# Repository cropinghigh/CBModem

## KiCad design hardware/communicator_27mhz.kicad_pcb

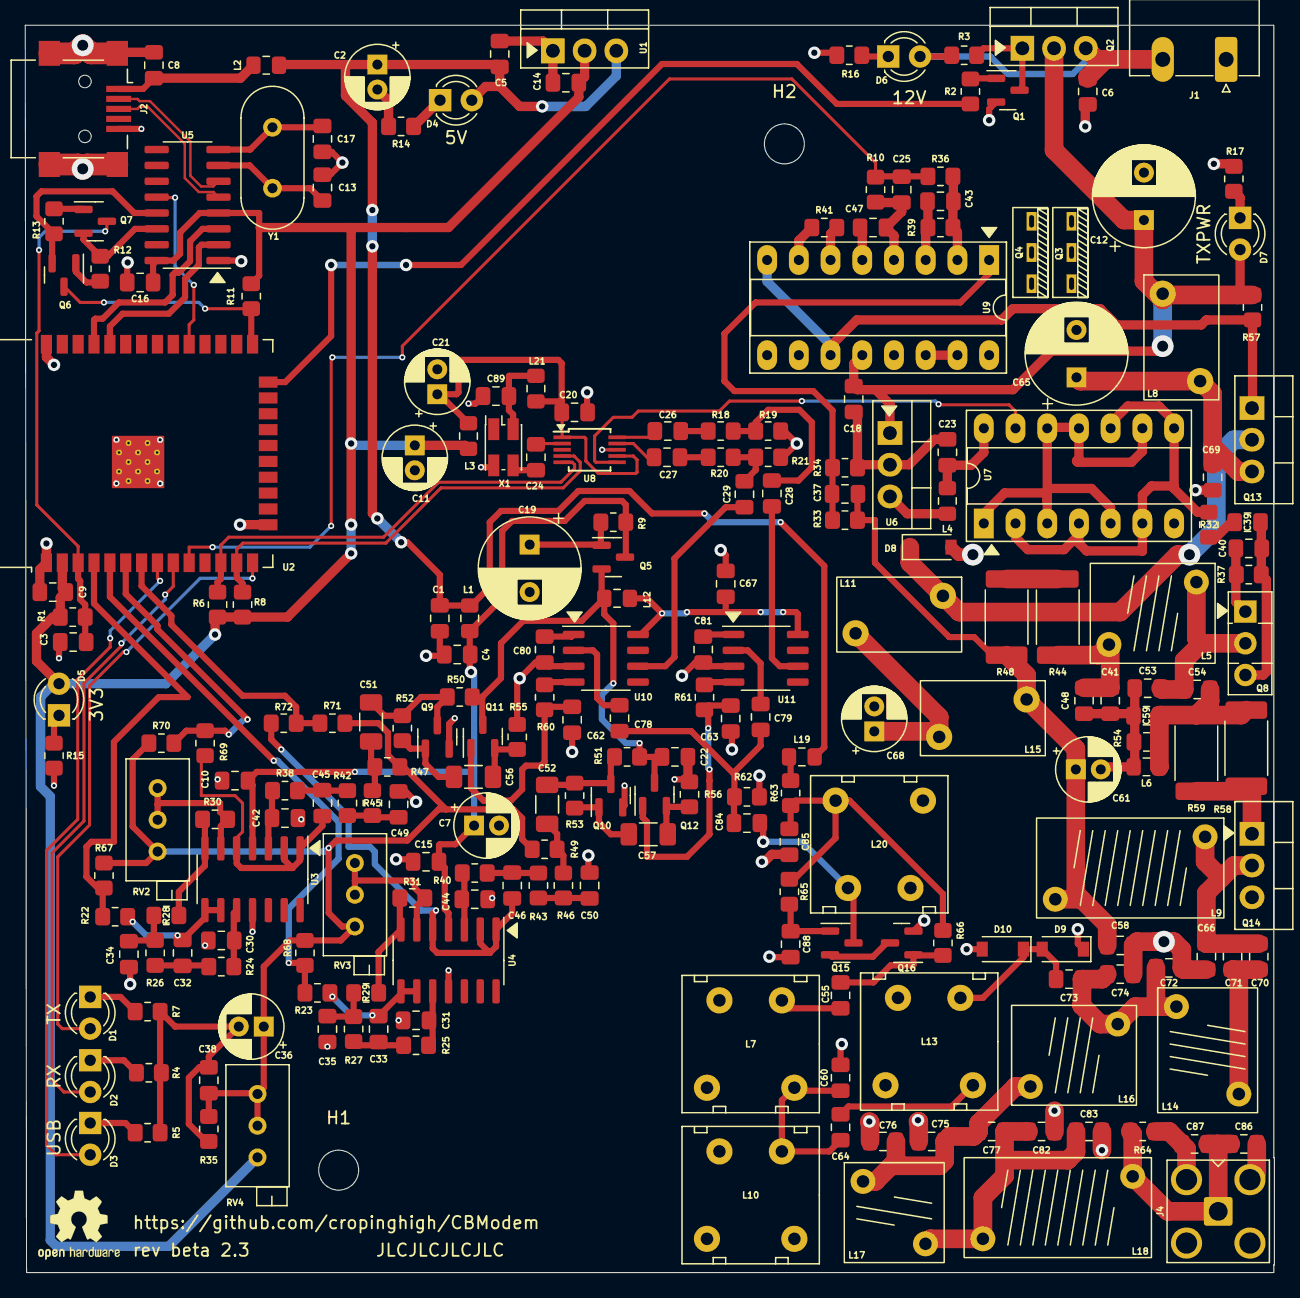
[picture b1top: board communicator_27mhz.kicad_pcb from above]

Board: 2 copper layers, 100.0 x 99.9 mm, 230 parts (0 on the bottom side), 132 nets.

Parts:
C1, C4, C5, C6, C8, C9, C10, C14, C15, C16, C18, C20, C23, C24, C26, C27, C28, C29, C38, C39, C43, C54, C58, C67, C69, C85, C89: 0.1u; C_0805_2012Metric_Pad1.18x1.45mm_HandSolder
C3: 2.2u; C_0805_2012Metric_Pad1.18x1.45mm_HandSolder
C7, C21, C36: 47u; CP_Radial_D5.0mm_P2.00mm
C11: 10u; CP_Radial_D5.0mm_P2.00mm
C12, C19: 470u; CP_Radial_D8.0mm_P3.80mm
C13, C17: 22p; C_0805_2012Metric_Pad1.18x1.45mm_HandSolder
C25, C32, C33, C34, C35, C45, C46, C49, C50, C62, C63, C78, C79, C80, C81, C88: 10n; C_0805_2012Metric_Pad1.18x1.45mm_HandSolder
C30, C31, C42, C44, C47: 1n; C_0805_2012Metric_Pad1.18x1.45mm_HandSolder
C37: 6n8; C_0805_2012Metric_Pad1.18x1.45mm_HandSolder
C40, C86: 150p; C_0805_2012Metric_Pad1.18x1.45mm_HandSolder
C41, C48: 47n; C_0805_2012Metric_Pad1.18x1.45mm_HandSolder
C51, C52, C56, C57: 10u; C_1206_3216Metric_Pad1.33x1.80mm_HandSolder
C53, C60, C72, C74, C75: 330p; C_0805_2012Metric_Pad1.18x1.45mm_HandSolder
C55, C64: 470p; C_0805_2012Metric_Pad1.18x1.45mm_HandSolder
C59, C66: 100p; C_0805_2012Metric_Pad1.18x1.45mm_HandSolder
C70, C71, C76, C82, C83: 220p; C_0805_2012Metric_Pad1.18x1.45mm_HandSolder
C73, C84: 47p; C_0805_2012Metric_Pad1.18x1.45mm_HandSolder
C77: 39p; C_0805_2012Metric_Pad1.18x1.45mm_HandSolder
C87: 30p; C_0805_2012Metric_Pad1.18x1.45mm_HandSolder
C?: 22u; CP_Radial_D8.0mm_P3.80mm
C?#2: 47u; CP_Radial_D5.0mm_P2.00mm
C?#3: 0.1u; C_0805_2012Metric_Pad1.18x1.45mm_HandSolder
C?#4, C?#5: 22u; CP_Radial_D5.0mm_P2.00mm
D1: TX; LED_D3.0mm
D2: RX; LED_D3.0mm
D3: USB; LED_D3.0mm
D4: 5V; LED_D3.0mm
D5: 3V3; LED_D3.0mm
D6: 12V; LED_D3.0mm
D7: TXPWR; LED_D3.0mm
D8, D9, D10: 4148; D_SOD-123
H1, H2: M3; MountingHole_3.2mm_M3
J1: EXT_12V; PhoenixContact_MC_1,5_2-G-5.08_1x02_P5.08mm_Horizontal
J2: USB_B_Micro; USB_Mini-B_Lumberg_2486_01_Horizontal
J4: ANT; SMA_Amphenol_901-143_Horizontal
L1, L2, L3, L4, L12, L19, L21: 10uH; L_0805_2012Metric_Pad1.15x1.40mm_HandSolder
L5: 0.15uH(6T,d6); Inductor_10x8
L6: 6.8uH; L_0805_2012Metric_Pad1.15x1.40mm_HandSolder
L7, L10: 220n; Soviet_inductor_core_vertical
L8, L15: ~40T on М2000НМ core; Ferrite_ring_10x6x5_vertical
L9: 0.5uH(13T,d5); Inductor_15x8
L11: 6T on М2000НМ core; Ferrite_ring_10x6x5_vertical
L13: 820n; Soviet_inductor_core_vertical
L14: 0.225uH(6T,d6); Inductor_10x8
L16: 6T, d=5; Inductor_10x8
L17: 7T, d=4; Inductor_8x8
L18: 10T, d=4mm; Inductor_15x8
L20: 3.7-20uH; Soviet_inductor_core_vertical
LOGO1: Logo_Open_Hardware_Large; OSHW-Logo2_7.3x6mm_SilkScreen
Q1: MMBT2222A; SOT-23
Q2, Q13: IRF9Z34N; TO-220-3_Vertical
Q3, Q4: KT315; KT-13
Q8: C2314; TO-126-3_Vertical
Q14: C2078; TO-220-3_Vertical
Q?: MMBT2222A; SOT-23
Q?#2, Q?#3, Q?#4, Q?#5, Q?#6, Q?#7, Q?#8, Q?#9: MMBT2222A; SOT-23
R1, R3, R11, R12, R13, R22, R23, R26, R27, R42, R43, R67, R68, R69, R70, R71, R72: 10k; R_0805_2012Metric_Pad1.20x1.40mm_HandSolder
R2: 50k; R_0805_2012Metric_Pad1.20x1.40mm_HandSolder
R4, R5, R6, R7, R8, R15: 1k; R_0805_2012Metric_Pad1.20x1.40mm_HandSolder
R9, R62: 680; R_0805_2012Metric_Pad1.20x1.40mm_HandSolder
R14: 2k; R_0805_2012Metric_Pad1.20x1.40mm_HandSolder
R16, R17, R34, R41, R47, R49, R50, R51: 5k; R_0805_2012Metric_Pad1.20x1.40mm_HandSolder
R18, R20: 6k8; R_0805_2012Metric_Pad1.20x1.40mm_HandSolder
R19, R21: 510; R_0805_2012Metric_Pad1.20x1.40mm_HandSolder
R24, R25, R38, R40: 5k6; R_0805_2012Metric_Pad1.20x1.40mm_HandSolder
R28, R29, R45, R46, R60, R61: 3k3; R_0805_2012Metric_Pad1.20x1.40mm_HandSolder
R30, R31: 20k; R_0805_2012Metric_Pad1.20x1.40mm_HandSolder
R32: 10; R_0805_2012Metric_Pad1.20x1.40mm_HandSolder
R35: 500; R_0805_2012Metric_Pad1.20x1.40mm_HandSolder
R36: 470; R_0805_2012Metric_Pad1.20x1.40mm_HandSolder
R37, R63: 100; R_0805_2012Metric_Pad1.20x1.40mm_HandSolder
R39, R52, R53: 100k; R_0805_2012Metric_Pad1.20x1.40mm_HandSolder
R44, R48, R58, R59: 5 1W; R_2512_6332Metric_Pad1.40x3.35mm_HandSolder
R54: 150; R_0805_2012Metric_Pad1.20x1.40mm_HandSolder
R55, R56: 900; R_0805_2012Metric_Pad1.20x1.40mm_HandSolder
R57: 330; R_0805_2012Metric_Pad1.20x1.40mm_HandSolder
R64: 4k7; R_0805_2012Metric_Pad1.20x1.40mm_HandSolder
R65, R66: 25k; R_0805_2012Metric_Pad1.20x1.40mm_HandSolder
R?: 20k; R_0805_2012Metric_Pad1.20x1.40mm_HandSolder
R?#2: 20k; R_0805_2012Metric_Pad1.20x1.40mm_HandSolder
RV2, RV3: 10k; Potentiometer_Bourns_3296X_Horizontal
RV?: 100k; Potentiometer_Bourns_3296X_Horizontal
U1: LM1117-3.3; TO-220-3_Vertical
U2: ESP32-WROOM-32
U3, U4: LM324; SOIC-14_3.9x8.7mm_P1.27mm
U5: CH340G; SOIC-16_3.9x9.9mm_P1.27mm
U6: L7805; TO-220-3_Vertical
U7: 74ACT14; DIP-14_W7.62mm_Socket_LongPads
U8: Si5351A; MSOP-10_3x3mm_P0.5mm
U9: TL494; DIP-16_W7.62mm_Socket_LongPads
U10, U11: SA612; SO-8_3.9x4.9mm_P1.27mm
X1: 3225 25 MHz TCXO; Oscillator_SMD_EuroQuartz_XO32-4Pin_3.2x2.5mm_HandSoldering
Y1: 12M; Crystal_HC49-4H_Vertical

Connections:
+3V3: C9.1, C11.1, C14.1, C16.2, D5.2 (A), L3.1, R1.1, R6.2, R8.2, R11.2, RV?.3, U1.2 (VO), U2.2 (VDD), U5.4 (V3), U5.16 (VCC)
+3V3FILT: C20.2, C21.1, L3.2, L21.2, U8.1 (VDD), U8.7 (VDDO)
+5V: C1.1, C5.1, C?#2.1, D4.2 (A), L1.1, L2.2, L19.2, U1.3 (VI)
+5VFILT: C4.1, C7.1, C10.1, C15.1, L1.2, Q?#3.3 (C), R9.1, U3.4 (V+), U4.4 (V+)
+5VMXR: C?#3.2, L12.1, Q?.3 (C), Q?#3.2 (E), Q?#8.3 (C), R50.1, R51.1
+5VTX: L4.1, U6.3 (OUT)
+12V: C6.1, D6.2 (A), J1.2, Q2.3 (S), R3.1
+12VTX: C12.1, C18.1, D7.2 (A), L8.2, Q2.2 (D), R57.1, U6.1 (IN), U9.12 (VCC)
/CLK_I: C27.1, U8.9 (CLK1)
/CLK_Q: C26.1, U8.10 (CLK0)
/RX_ANT_CLAMPED: C73.2, D9.2 (A), D10.1 (K), L13.2
/SCL: R8.1, U2.13 (IO14), U8.4 (SCL)
/SDA: R6.1, U2.12 (IO27), U8.5 (SDA)
/UD+: J2.3 (D+), U5.5 (UD+)
/UD-: J2.2 (D-), U5.6 (UD-)
ADCIN_I: R22.1, R67.2, U2.4 (SENSOR_VP)
ADCIN_LOW_I: R69.1, R70.2, U2.6 (IO34)
ADCIN_LOW_Q: R71.1, R72.2, U2.7 (IO35)
ADCIN_Q: R23.1, R68.1, U2.5 (SENSOR_VN)
GND: C1.2, C3.2, C4.2, C5.2, C6.2, C7.2, C8.2, C9.2, C10.2, C11.2, C12.2, C13.2, C14.2, C15.2, C16.1, C17.2, C18.2, C19.2, C20.1, C21.2, C23.2, C25.2, C30.2, C31.2, C34.2, C35.2, C36.2, C38.2, C40.1, C41.2, C42.2, C44.2, C47.1, C48.2, C49.2, C50.2, C53.2, C58.2, C59.2, C60.2, C62.2, C63.2, C66.2, C67.2, C69.2, C72.2, C74.2, C75.2, C76.2, C80.2, C81.2, C82.2, C83.2, C85.2, C86.2, C87.2, C88.1, C89.2, C?.2, C?#2.2, C?#3.1, C?#4.2, C?#5.2, D8.2 (A), D9.1 (K), D10.2 (A), J1.1, J2.5 (GND), J2.6 (Shield), J4.2 (Ext), L6.2, L10.1, Q1.2 (E), Q3.1 (B), Q3.2 (C), Q3.3 (E), Q4.1 (B), Q4.2 (C), Q4.3 (E), Q8.1 (E), Q14.3 (E), Q?#4.2 (E), Q?#6.2 (E), Q?#9.2 (E), R4.2, R5.1, R7.2, R14.2, R15.2, R16.2, R17.2, R19.1, R21.1, R34.2, R35.2, R37.2, R41.2, R54.2, R55.2, R56.2, R62.2, R64.2, R?.1, U1.1 (GND), U2.1 (GND), U2.15 (GND), U2.38 (GND), U2.39 (GND), U3.11 (V-), U4.11 (V-), U5.1 (GND), U6.2 (GND), U7.7 (GND), U8.8 (GND), U9.4 (DTC), U9.7 (GND), U9.9 (E1), U9.10 (E2), U9.13 (OUTCTRL), U9.16 (2IN+), U10.3 (GND), U11.3 (GND), X1.2 (GND)
LO_RX_I: C29.2, U10.6 (OSC_B)
LO_RX_Q: C28.1, U11.6 (OSC_B)
LO_TX: U7.13, U8.6 (CLK2)
MCU_DCD: U2.29 (IO5), U5.12 (~DCD)
MCU_EN: C3.1, Q?#7.3 (C), R1.2, U2.3 (EN)
MCU_G0: Q?#2.3 (C), R11.1, U2.25 (IO0)
MCU_RXD: U2.34 (RXD0/IO3), U5.2 (TXD)
MCU_TXD: U2.35 (TXD0/IO1), U5.3 (RXD)
unnamed: C8.1, J2.1 (VBUS), L2.1
unnamed: C13.1, U5.7 (XI), Y1.1
unnamed: C17.1, U5.8 (XO), Y1.2
unnamed: C19.1, Q?#3.1 (B), R9.2
unnamed: C23.1, L4.2, U7.14 (VCC)
unnamed: C24.1, X1.3 (OUT)
unnamed: C24.2, U8.2 (XA)
unnamed: C26.2, R18.2
unnamed: C27.2, R20.2
unnamed: C28.2, R18.1, R19.2
unnamed: C29.1, R20.1, R21.2
unnamed: C30.1, R24.2, U3.10 (+)
unnamed: C31.1, R25.2, U4.10 (+)
unnamed: C32.1, R24.1, R26.2
unnamed: C32.2, R22.2, U3.8, U3.9 (-)
unnamed: C33.1, R25.1, R27.2
unnamed: C33.2, R23.2, U4.8, U4.9 (-)
unnamed: C34.1, R26.1, R28.2
unnamed: C35.1, R27.1, R29.2
unnamed: C37.1, C58.1, C?#4.1, L9.1, L15.2, R48.2, R?#2.1
unnamed: C37.2, R34.1, R?#2.2, U9.1 (1IN+)
unnamed: C39.1, R32.2
unnamed: C39.2, C40.2, Q8.3 (B), R37.1
unnamed: C41.1, C48.1, L5.1, R44.1
unnamed: C42.1, R38.2, U3.3 (+)
unnamed: C43.1, R36.2, R39.2, U9.2 (1IN-)
unnamed: C43.2, R39.1, U9.3 (FB)
unnamed: C44.1, R40.2, U4.3 (+)
unnamed: C45.1, R38.1, R42.2
unnamed: C45.2, R69.2, U3.1, U3.2 (-), U3.5 (+)
unnamed: C46.1, R40.1, R43.2
unnamed: C46.2, R72.1, U4.1, U4.2 (-), U4.5 (+)
unnamed: C47.2, U9.5 (CT)
unnamed: C49.1, R42.1, R45.2
unnamed: C50.1, R43.1, R46.2
unnamed: C51.1, Q?#6.3 (C), R50.2, R52.1
unnamed: C51.2, R45.1, R47.1
unnamed: C52.1, Q?#4.3 (C), R51.2, R53.1
unnamed: C52.2, R46.1, R49.1
unnamed: C53.1, C54.2, L5.2, Q8.2 (C)
unnamed: C54.1, C59.1, L6.1, R54.1, R58.2, R59.1
unnamed: C55.2, L7.2
unnamed: C56.1, Q?.2 (E), R55.1
unnamed: C56.2, Q?#6.1 (B), R52.2
unnamed: C57.1, Q?#8.2 (E), R56.1
unnamed: C57.2, Q?#4.1 (B), R53.2
unnamed: C60.1, C64.1, L7.1, L10.2
unnamed: C62.1, Q?.1 (B), R60.2
unnamed: C63.1, Q?#8.1 (B), R61.2
unnamed: C64.2, L13.1
unnamed: C69.1, C?.1, L8.1, Q13.3 (S)
unnamed: C66.1, C70.2, C71.2, L9.2, Q14.2 (C)
unnamed: C67.1, L12.2, U10.8 (VCC), U11.8 (VCC)
unnamed: C?#5.1, L11.1, L15.1
unnamed: C70.1, C71.1, L14.1
unnamed: C72.1, C73.1, C74.1, L14.2, L16.1
unnamed: C75.1, C76.1, C77.1, L16.2, L17.2
unnamed: C77.2, C82.1, C83.1, L17.1, L18.1
unnamed: C78.1, C79.1, C84.2, R62.1
unnamed: C78.2, U10.2 (IN_B)
unnamed: C79.2, U11.2 (IN_B)
unnamed: C80.1, U10.1 (IN_A)
unnamed: C81.1, U11.1 (IN_A)
unnamed: C84.1, L20.2, Q?#5.3 (C)
unnamed: C85.1, L20.1, R63.2, R65.1, R66.1
unnamed: C86.1, C87.1, J4.1 (In), L18.2, R64.1
unnamed: C88.2, Q?#5.1 (B), R65.2
unnamed: C89.1, L21.1, X1.4 (Vcc)
unnamed: D1.1 (K), R7.1
unnamed: D1.2 (A), U2.14 (IO12)
unnamed: D2.1 (K), R4.1
unnamed: D2.2 (A), U2.9 (IO33)
unnamed: D3.1 (K), R5.2
unnamed: D3.2 (A), U2.8 (IO32)
unnamed: D4.1 (K), R14.1
unnamed: D5.1 (K), R15.1
unnamed: D6.1 (K), R16.1
unnamed: D7.1 (K), R17.1
unnamed: D8.1 (K), L11.2, Q13.2 (D)
unnamed: L19.1, R63.1
unnamed: Q1.1 (B), R2.1
unnamed: Q1.3 (C), Q2.1 (G), R3.2
unnamed: Q?#2.1 (B), R12.2
unnamed: Q?#2.2 (E), R13.1, U5.13 (~DTR)
unnamed: Q?#7.1 (B), R13.2
unnamed: Q?#7.2 (E), R12.1, U5.14 (~RTS)
unnamed: Q13.1 (G), R57.2, U9.8 (C1), U9.11 (C2)
unnamed: Q14.1 (B), R58.1, R59.2
unnamed: Q?#5.2 (E), Q?#9.3 (C)
unnamed: R28.1, R30.1, U3.7
unnamed: R29.1, R31.1, U4.7
unnamed: R30.2, RV2.1, RV2.2, U3.6 (-)
unnamed: R31.2, RV3.1, RV3.2, U4.6 (-)
unnamed: R32.1, U7.2, U7.4, U7.6, U7.8, U7.10
unnamed: R41.1, U9.6 (RT)
unnamed: R44.2, R48.1
unnamed: R60.1, U10.4 (OUT_A)
unnamed: R61.1, U11.4 (OUT_A)
unnamed: U7.1, U7.3, U7.5, U7.9, U7.11, U7.12
unnamed: U9.14 (REF), U9.15 (2IN-)
RX_AMP_REF_V: C36.1, C38.1, R35.1, R47.2, R49.2, R67.1, R68.2, R70.1, R71.2, RV2.3, RV3.3, RV?.1, RV?.2
RX_IN_ANT: C55.1, Q?#9.1 (B), R66.2
TXAMPL_V: C25.1, R36.1, R?.2, U2.10 (IO25)
TXPENABLE: R2.2, U2.24 (IO2)

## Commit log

2021-06-10 pcb redesign
2021-10-18 rewrite code in C, remove useless files
2021-10-19 software updates
2022-09-02 schematic updates
2022-09-02 schematic update 2
2022-09-13 split code into headers
2022-09-13 software build system update
2022-11-12 partial schematic update
2022-11-18 another in-progress schematic update
2022-11-28 another WIP commit
2022-12-03 almost ready sch+pcb
2022-12-03 avoid possible adc overload
2022-12-04 finish PCB v beta2.3, prepare for jlcpcb
2022-12-09 start firmware development
2023-01-17 hardwarelibs almost done
2023-02-05 hwlibs update & dsp beginning
2023-02-10 dsp tx, clock recovery, simple bfsk mod/demod
2023-02-14 rm old fw&start mfsk&tr update
2023-02-18 msk mod+demod + adc bugfix
2023-02-26 pc app+params+many other
2023-03-02 basic functions almost done + schematic upd
2023-03-06 AFC update
2023-03-21 Create LICENSE
2024-03-16 split pc lib and app
2024-03-24 qcbmctl
2024-03-24 various fixes
2024-03-24 minor speed improvement
2024-03-25 fix for single core machines
